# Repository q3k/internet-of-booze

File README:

HSVending interface firmware

To make, you'll need arm-none-eabi.

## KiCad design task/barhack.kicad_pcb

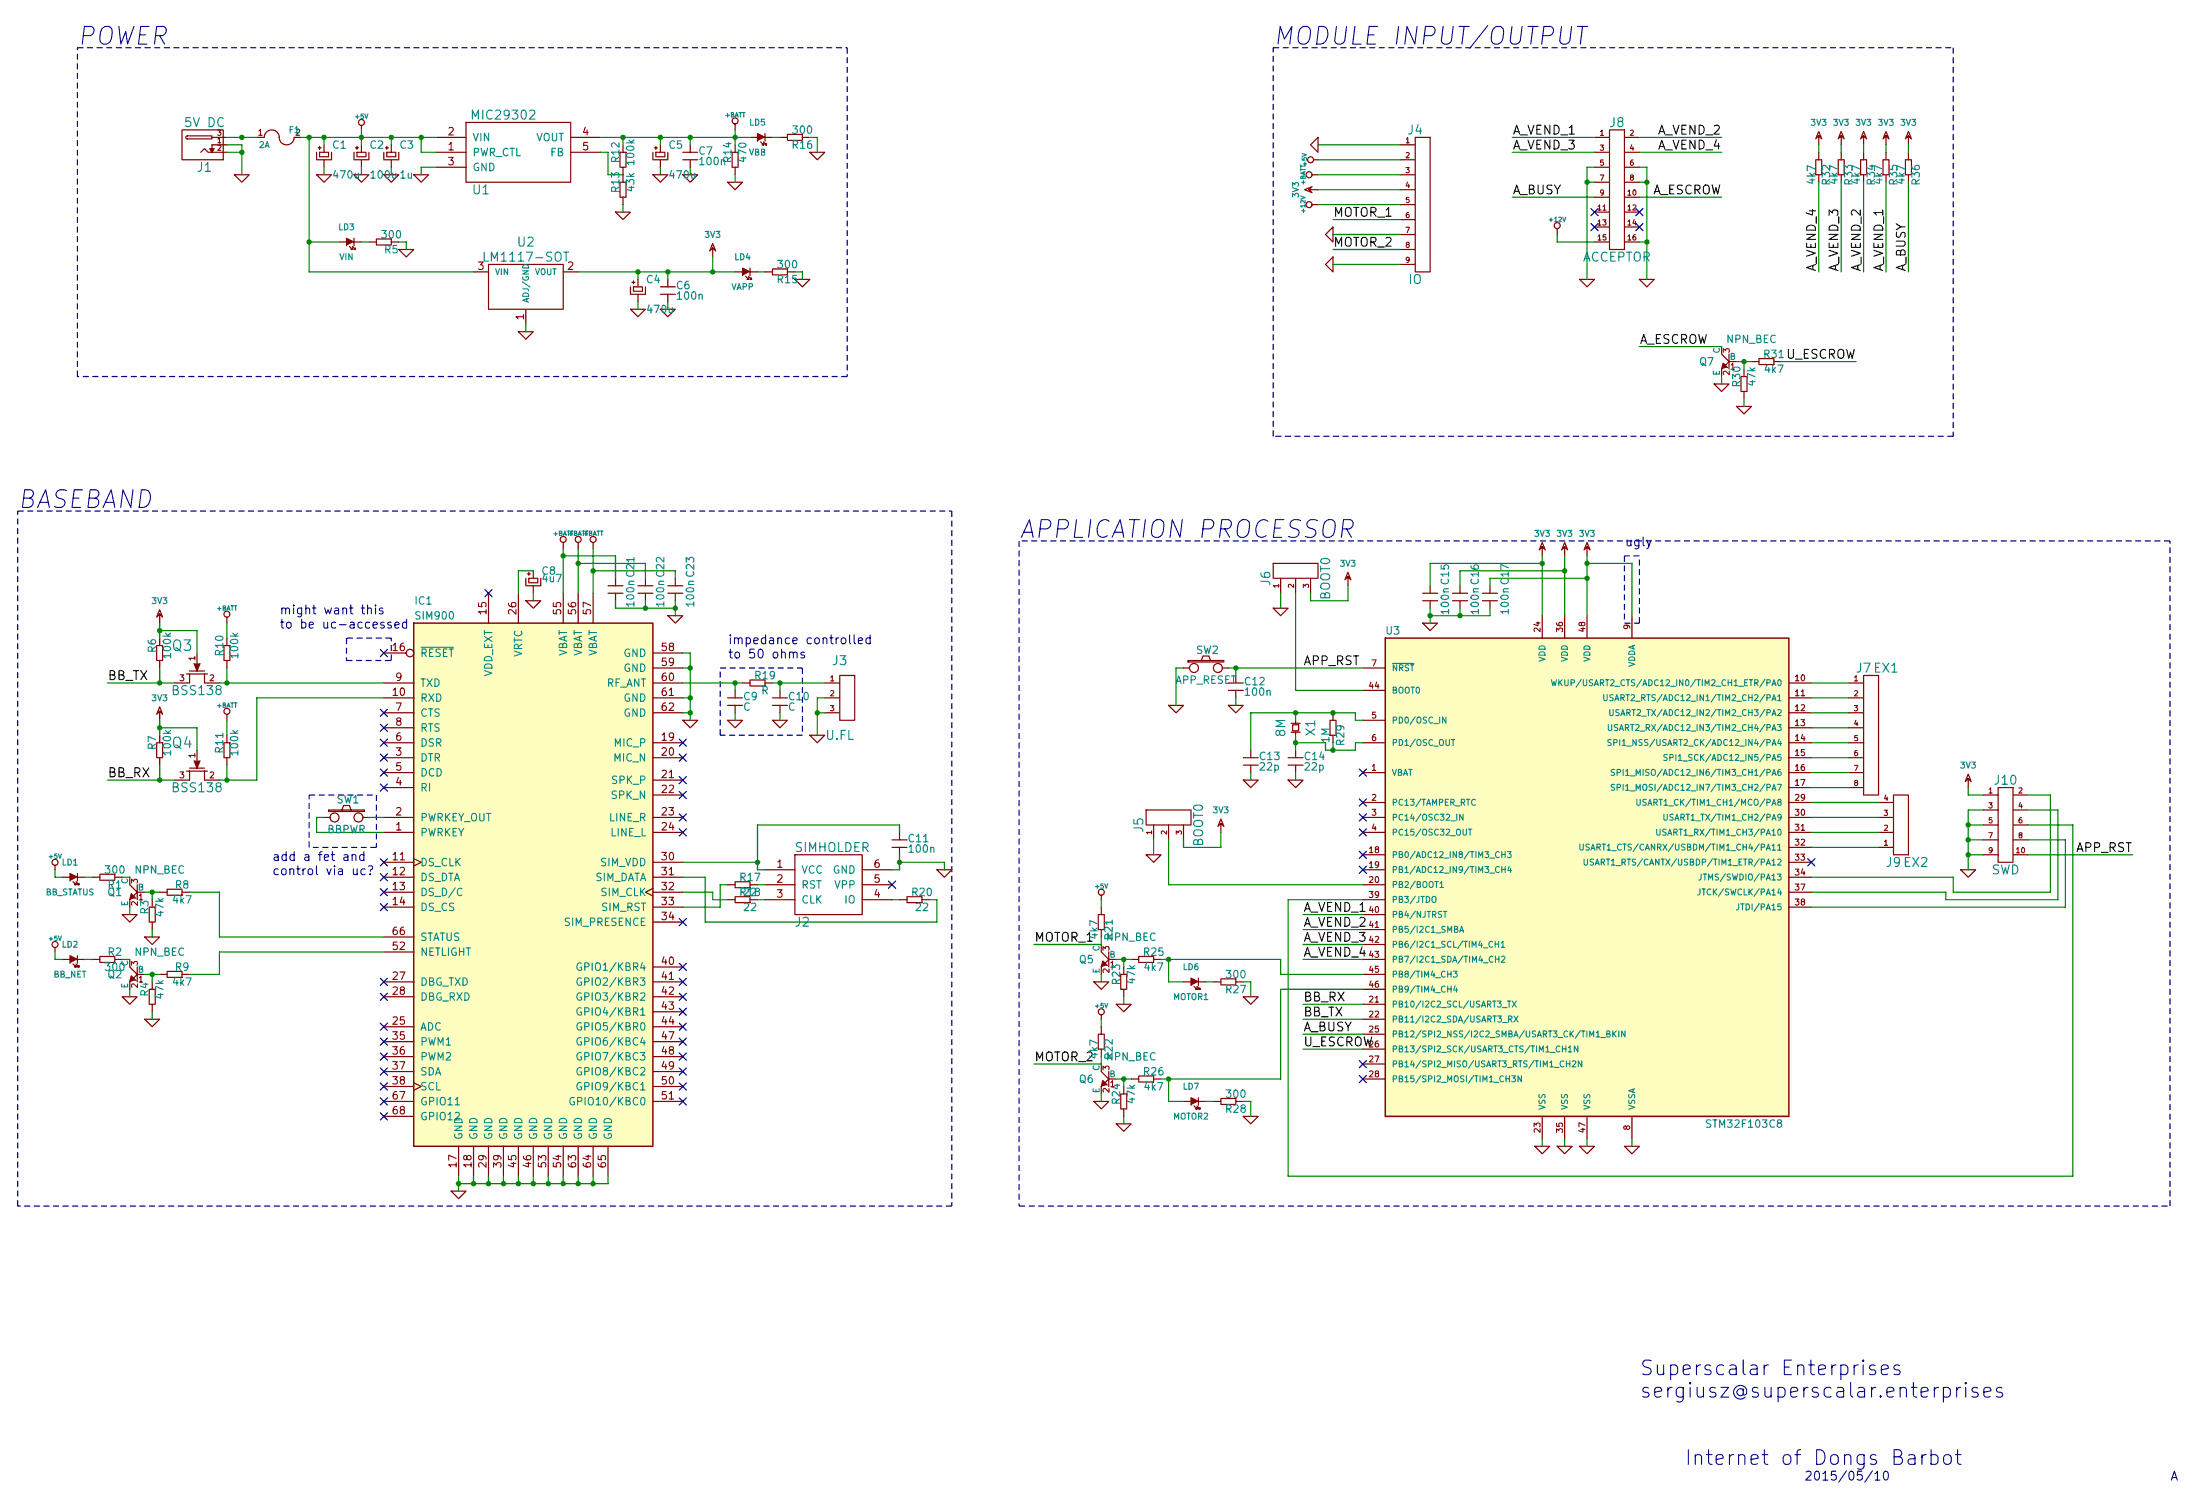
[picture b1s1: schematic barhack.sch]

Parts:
C1, C4, C5: 470u; c_elec_8x10
C2: 100u; c_tant_C
C3: 1u; c_0603
C6, C7, C11, C12, C15, C16, C17, C21, C22, C23: 100n; c_0603
C8: 4u7; c_0603
C9, C10: C; c_0603
C13, C14: 22p; c_0603
F1: 2A; fuse_holder_CQ-2
IC1: SIM900
J1: 5V DC; dc_socket
J2: SIMHOLDER; C707-10M006-049-2
J3: U.FL; coaxial_u.fl-r-smt-1
J4: IO; mstbva_2,5%2f9-g-5,08
J5, J6: BOOT0; pin_strip_3
J7: EX1; pin_strip_4x2
J8: ACCEPTOR; pin_strip_8x2
J9: EX2; pin_strip_2x2
J10: SWD; pin_strip_5x2
LD1: BB_STATUS; Led_0603
LD2: BB_NET; Led_0603
LD3: VIN; Led_0603
LD4: VAPP; Led_0603
LD5: VBB; Led_0603
LD6: MOTOR1; Led_0603
LD7: MOTOR2; Led_0603
Q1, Q2, Q5, Q6, Q7: NPN_BEC; sot23
Q3, Q4: BSS138; sot23
R1, R2, R5, R15, R16, R27, R28: 300; r_0603
R3, R4, R23, R24, R30: 47k; r_0603
R6, R7, R10, R11, R12: 100k; r_0603
R8, R9, R21, R22, R25, R26, R31, R32, R33, R34, R35, R36: 4k7; r_0603
R13: 43k; r_0603
R14: 470; r_0603
R17, R18, R20: 22; r_0603
R19: R; r_0603
R29: 1M; r_0603
SW1: BBPWR; smd_push
SW2: APP_RESET; smd_push
U1: MIC29302; d-pak-5
U2: LM1117-SOT; d-pak
U3: STM32F103C8; lqfp48
X1: 8M; hc-49_smd

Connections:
3V3: C4.1, C6.1, C15.1, C16.1, C17.1, J4.4, J5.3, J6.3, J10.1, LD4.1 (A), Q3.1 (G), Q4.1 (G), R6.1, R7.1, R32.2, R33.2, R34.2, R35.2, R36.2, U2.2 (VOUT), U3.9 (VDDA), U3.24 (VDD), U3.36 (VDD), U3.48 (VDD)
+5V: C1.1, C2.1, C3.1, F1.2, J4.2, LD1.1 (A), LD2.1 (A), LD3.1 (A), R21.2, R22.2, U1.1 (PWR_CTL), U1.2 (VIN), U2.3 (VIN)
+12V: J4.5, J8.15
+BATT: C5.1, C7.1, C21.1, C22.1, C23.1, IC1.55 (VBAT), IC1.56 (VBAT), IC1.57 (VBAT), J4.3, LD5.1 (A), R10.1, R11.1, R12.1, R14.1, U1.4 (VOUT)
/APP_RST: C12.1, J10.10, SW2.2, U3.7 (~NRST)
/A_BUSY: J8.9, R36.1, U3.25 (PB12/SPI2_NSS/I2C2_SMBA/USART3_CK/TIM1_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)
/A_ESCROW: J8.10, Q7.3 (C)
/A_VEND_1: J8.1, R35.1, U3.40 (PB4/NJTRST)
/A_VEND_2: J8.2, R34.1, U3.41 (PB5/I2C1_SMBA)
/A_VEND_3: J8.3, R33.1, U3.42 (PB6/I2C1_SCL/TIM4_CH1)
/A_VEND_4: J8.4, R32.1, U3.43 (PB7/I2C1_SDA/TIM4_CH2)
/BB_RX: Q4.3 (D), R7.2, U3.21 (PB10/I2C2_SCL/USART3_TX)
/BB_TX: Q3.3 (D), R6.2, U3.22 (PB11/I2C2_SDA/USART3_RX)
/MOTOR_1: J4.6, Q5.3 (C), R21.1
/MOTOR_2: J4.8, Q6.3 (C), R22.1
/U_ESCROW: R31.1, U3.26 (PB13/SPI2_SCK/USART3_CTS/TIM1_CH1N)
GND: C1.2, C2.2, C3.2, C4.2, C5.2, C6.2, C7.2, C8.2, C9.2, C10.2, C11.2, C12.2, C13.2, C14.2, C15.2, C16.2, C17.2, C21.2, C22.2, C23.2, IC1.17 (GND), IC1.18 (GND), IC1.29 (GND), IC1.39 (GND), IC1.45 (GND), IC1.46 (GND), IC1.53 (GND), IC1.54 (GND), IC1.58 (GND), IC1.59 (GND), IC1.61 (GND), IC1.62 (GND), IC1.63 (GND), IC1.64 (GND), IC1.65 (GND), J1.1, J1.2, J2.6 (GND), J3.2, J3.3, J4.1, J4.7, J4.9, J5.1, J6.1, J8.5, J8.6, J8.7, J8.8, J8.16, J10.3, J10.5, J10.7, J10.9, Q1.2 (E), Q2.2 (E), Q5.2 (E), Q6.2 (E), Q7.2 (E), R3.2, R4.2, R5.1, R13.2, R14.2, R15.1, R16.1, R23.2, R24.2, R27.1, R28.1, R30.2, SW2.1, U1.3 (GND), U2.1 (ADJ/GND), U3.8 (VSSA), U3.23 (VSS), U3.35 (VSS), U3.47 (VSS)
unnamed: C8.1, IC1.26 (VRTC)
unnamed: C9.1, IC1.60 (RF_ANT), R19.2
unnamed: C10.1, J3.1, R19.1
unnamed: C11.1, IC1.30 (SIM_VDD), J2.1 (VCC)
unnamed: C13.1, R29.2, U3.5 (PD0/OSC_IN), X1.1
unnamed: C14.1, R29.1, U3.6 (PD1/OSC_OUT), X1.2
unnamed: F1.1, J1.3
unnamed: IC1.1 (PWRKEY), SW1.1
unnamed: IC1.2 (PWRKEY_OUT), SW1.2
unnamed: IC1.9 (TXD), Q3.2 (S), R10.2
unnamed: IC1.10 (RXD), Q4.2 (S), R11.2
unnamed: IC1.31 (SIM_DATA), R20.1
unnamed: IC1.32 (SIM_CLK), R18.2
unnamed: IC1.33 (SIM_RST), R17.2
unnamed: IC1.52 (NETLIGHT), R9.1
unnamed: IC1.66 (STATUS), R8.1
unnamed: J2.2 (RST), R17.1
unnamed: J2.3 (CLK), R18.1
unnamed: J2.4 (IO), R20.2
unnamed: J5.2, U3.20 (PB2/BOOT1)
unnamed: J6.2, U3.44 (BOOT0)
unnamed: J7.1, U3.10 (WKUP/USART2_CTS/ADC12_IN0/TIM2_CH1_ETR/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)
unnamed: J7.2, U3.11 (USART2_RTS/ADC12_IN1/TIM2_CH2/PA1)
unnamed: J7.3, U3.12 (USART2_TX/ADC12_IN2/TIM2_CH3/PA2)
unnamed: J7.4, U3.13 (USART2_RX/ADC12_IN3/TIM2_CH4/PA3)
unnamed: J7.5, U3.14 (SPI1_NSS/USART2_CK/ADC12_IN4/PA4)
unnamed: J7.6, U3.15 (SPI1_SCK/ADC12_IN5/PA5)
unnamed: J7.7, U3.16 (SPI1_MISO/ADC12_IN6/TIM3_CH1/PA6)
unnamed: J7.8, U3.17 (SPI1_MOSI/ADC12_IN7/TIM3_CH2/PA7)
unnamed: J9.1, U3.32 (USART1_CTS/CANRX/USBDM/TIM1_CH4/PA11)
unnamed: J9.2, U3.31 (USART1_RX/TIM1_CH3/PA10)
unnamed: J9.3, U3.30 (USART1_TX/TIM1_CH2/PA9)
unnamed: J9.4, U3.29 (USART1_CK/TIM1_CH1/MCO/PA8)
unnamed: J10.2, U3.34 (JTMS/SWDIO/PA13)
unnamed: J10.4, U3.37 (JTCK/SWCLK/PA14)
unnamed: J10.6, U3.39 (PB3/JTDO)
unnamed: J10.8, U3.38 (JTDI/PA15)
unnamed: LD1.2 (K), R1.2
unnamed: LD2.2 (K), R2.2
unnamed: LD3.2 (K), R5.2
unnamed: LD4.2 (K), R15.2
unnamed: LD5.2 (K), R16.2
unnamed: LD6.1 (A), R25.1, U3.45 (PB8/TIM4_CH3)
unnamed: LD6.2 (K), R27.2
unnamed: LD7.1 (A), R26.1, U3.46 (PB9/TIM4_CH4)
unnamed: LD7.2 (K), R28.2
unnamed: Q1.1 (B), R3.1, R8.2
unnamed: Q1.3 (C), R1.1
unnamed: Q2.1 (B), R4.1, R9.2
unnamed: Q2.3 (C), R2.1
unnamed: Q5.1 (B), R23.1, R25.2
unnamed: Q6.1 (B), R24.1, R26.2
unnamed: Q7.1 (B), R30.1, R31.2
unnamed: R12.2, R13.1, U1.5 (FB)

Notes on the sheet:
Internet of Dongs Barbot
Superscalar Enterprises
sergiusz@superscalar.enterprises
2015/05/10
impedance controlled to 50 ohms
might want this to be uc-accessed
add a fet and control via uc?
ugly
POWER
MODULE INPUT/OUTPUT
APPLICATION PROCESSOR
BASEBAND

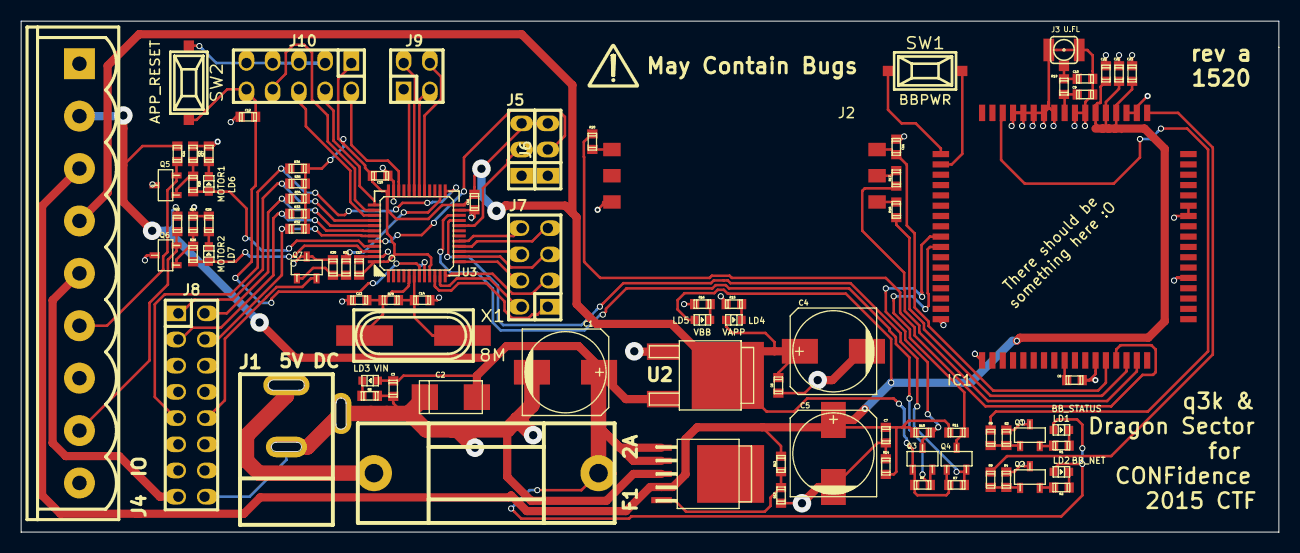
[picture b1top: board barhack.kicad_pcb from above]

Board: 2 copper layers, 121.9 x 49.5 mm, 88 parts (0 on the bottom side), 71 nets.

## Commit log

2013-11-17 Initial commit.
2013-11-18 Refactored code structure
2013-11-18 dos2unix'd main.c
2013-11-18 Fixed indentation in main.c
2013-11-18 clean up main.c
2015-05-10 Basic electronics schematic.
2015-05-10 Basic task structure.
2015-05-10 Reorder stuff around.
2015-05-10 Remove footprint of U3 from schematic.
2015-05-10 I don't think this needs to be in the repo.
2015-05-11 Fiiiiinal design for CONFidence, sent off to fab house.
2015-05-13 Change via physical sizes (to increase copper surface), resend to Satland.
2015-05-13 Fix CMSIS for new gcc (>=4.8)
2015-05-13 Change over to STM32F103 (from 100).
2015-05-14 Some basic comms code.
2015-05-23 SMS receiving works
2015-05-24 It kinda works!
2015-05-25 h00axek11!!
2015-05-25 pwn2
2015-05-25 Almost final version.
2015-05-25 Introduction
2015-05-25 Fix Makefile
2015-05-25 Update description and resource.
2015-05-25 Preliminary description.
2015-05-25 Pwn meta
2015-05-25 Pwn.
2015-05-25 Final fixes.
2015-05-25 Update description.txt (typos).
2015-05-26 Hint
2015-05-26 Reorganize stuff around.
2015-05-26 License, and releae.
